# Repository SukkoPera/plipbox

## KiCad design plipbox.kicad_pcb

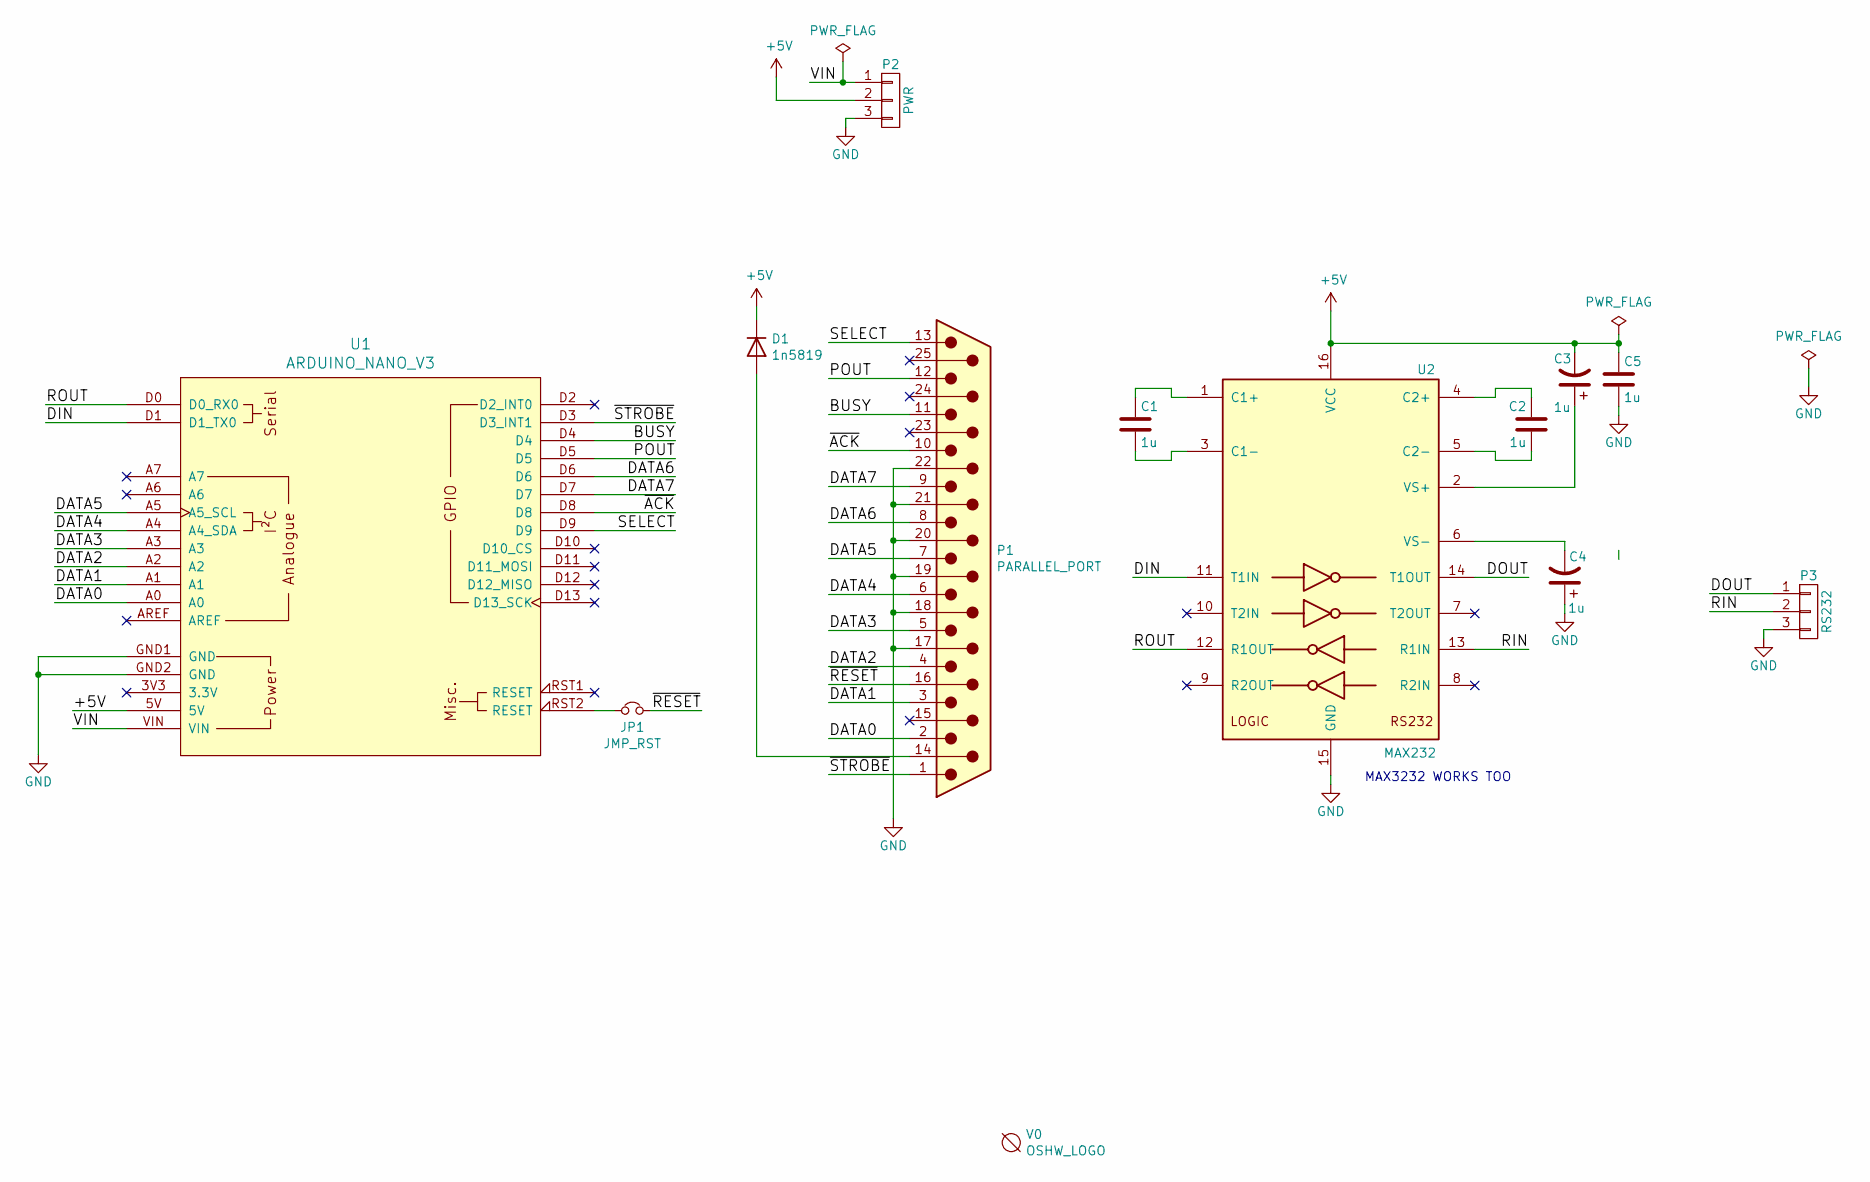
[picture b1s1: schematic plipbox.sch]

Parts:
C1, C2, C3, C4, C5: 1u; C_0805_2012Metric_Pad1.18x1.45mm_HandSolder
D1: 1n5819; D_SMA
JP1: JMP_RST; SolderJumper-2_P1.3mm_Open_RoundedPad1.0x1.5mm
P1: PARALLEL_PORT; DSUB-25_Male_EdgeMount_P2.77mm
P2: PWR; Pin_Header_Straight_1x03-ModSilkS
P3: RS232; Pin_Header_Straight_1x03-ModSilkS
U1: ARDUINO_NANO_V3; Arduino_Nano_Socket
U2: MAX232; SOIC-16_3.9x9.9mm_P1.27mm
V0: OSHW_LOGO; OSHW-Logo2_9.8x8mm_Copper

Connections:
+5V: C3.2, C5.1, D1.1 (K), P2.2, U1.5V, U2.16 (VCC)
/BUSY: P1.11, U1.D4
/DATA0: P1.2, U1.A0
/DATA1: P1.3, U1.A1
/DATA2: P1.4, U1.A2
/DATA3: P1.5, U1.A3
/DATA4: P1.6, U1.A4 (A4_SDA)
/DATA5: P1.7, U1.A5 (A5_SCL)
/DATA6: P1.8, U1.D6
/DATA7: P1.9, U1.D7
/DIN: U1.D1 (D1_TX0), U2.11 (T1IN)
/DOUT: P3.1, U2.14 (T1OUT)
/POUT: P1.12, U1.D5
/RIN: P3.2, U2.13 (R1IN)
/ROUT: U1.D0 (D0_RX0), U2.12 (R1OUT)
/SELECT: P1.13, U1.D9
/VIN: P2.1, U1.VIN
/~ACK: P1.10, U1.D8
/~RESET: JP1.2, P1.16
/~STROBE: P1.1, U1.D3 (D3_INT1)
GND: C4.1, C5.2, P1.17, P1.18, P1.19, P1.20, P1.21, P1.22, P2.3, P3.3, U1.GND1 (GND), U1.GND2 (GND), U2.15 (GND)
unnamed: C1.1, U2.1 (C1+)
unnamed: C1.2, U2.3 (C1-)
unnamed: C2.1, U2.4 (C2+)
unnamed: C2.2, U2.5 (C2-)
unnamed: C3.1, U2.2 (VS+)
unnamed: C4.2, U2.6 (VS-)
unnamed: D1.2 (A), P1.14
unnamed: JP1.1, U1.RST2 (RESET)

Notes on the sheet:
MAX3232 WORKS TOO

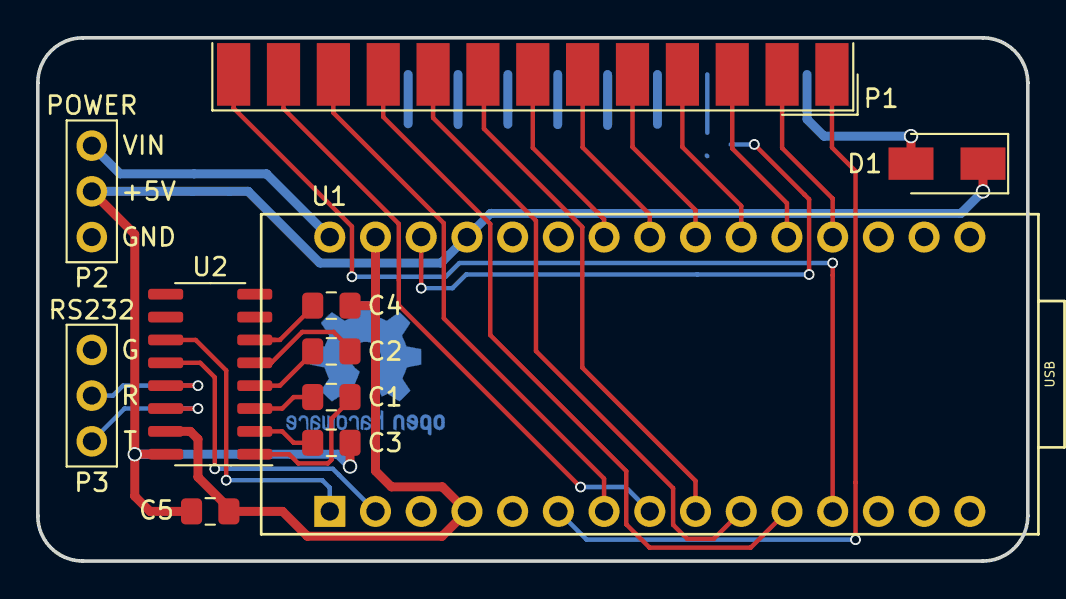
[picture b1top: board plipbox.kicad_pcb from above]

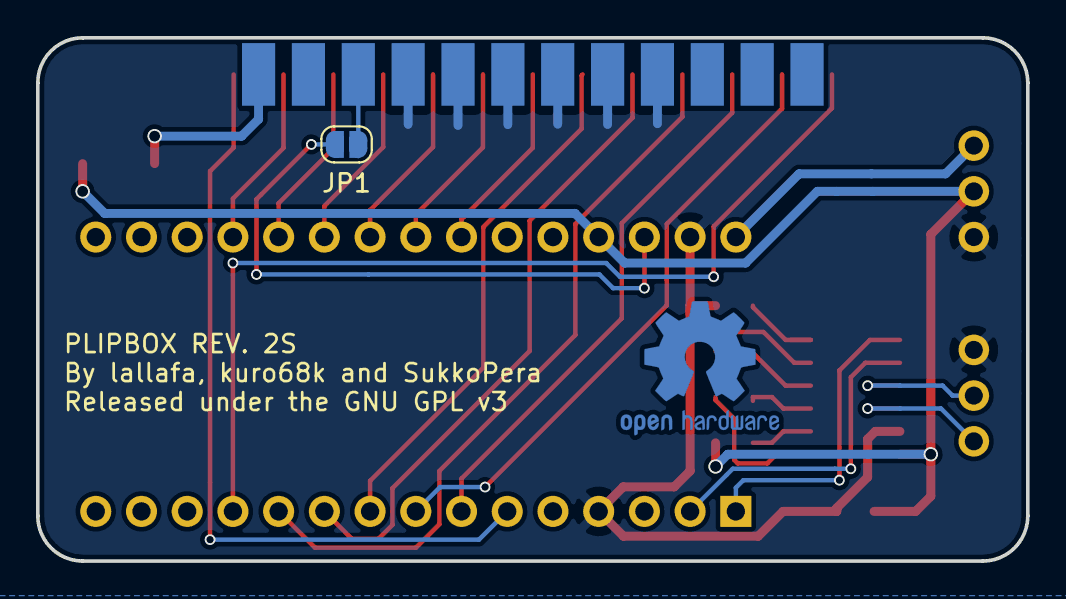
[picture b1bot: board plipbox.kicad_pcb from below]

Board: 2 copper layers, 55.0 x 29.1 mm, 13 parts (2 on the bottom side), 29 nets.

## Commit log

2020-12-31 Use edge connector, use MAX232 & other minor tweaks
2021-08-31 Add diode and fix C3 C3 was WRONG in Rev.1S, it needs to be between pin 2 of U1 and VCC, not GND. The diode should only be mounted if the Amiga is modded so that power on the +5V line is not limited.
2023-02-28 Add reset jumper and ready for V2S

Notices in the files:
plipbox.kicad_pcb:
Released under the GNU GPL v3
